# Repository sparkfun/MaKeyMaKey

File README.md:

**Note: Retired Product**
===========

This product has been retired from our catalog and is no longer for sale. This page is made available for those looking for datasheets and the simply curious. For the latest version of the board manufactured by JoyLabz, check out the [Makey Makey Classic by JoyLabz](https://www.sparkfun.com/products/14478).

---

MaKey MaKey
===========

[  
*MaKey MaKey - Standard Kit (WIG-11511)*](https://www.sparkfun.com/products/11511)

Using the MaKey MaKey you can *make* anything into a *key* (get it?) just by connecting a few alligator clips. The MaKey MaKey is an invention kit that tricks your computer into thinking that almost anything is a keyboard. This allows you to hook up all kinds of fun things as an input.

The MaKey MaKey uses high resistance switching to detect when you've made a connection even through materials that aren't very conductive (like leaves, pasta or people). This technique attracts noise on the input, so a moving window averager is used to lowpass the noise. The on-board ATMega32u4 communicates with your computer using the Human Interface Device (HID) protocol which means that it can act like a keyboard or mouse.

Repository Contents
-------------------
* **/Firmware** - Example firmware files
* **/Hardware** - All Eagle design files (.brd, .sch)
* **/Production** - Test bed files and production panel files

Documentation
--------------
* **[Makey Makey Quickstart Guide](https://learn.sparkfun.com/tutorials/makey-makey-quickstart-guide)** - Basic hookup guide for the Makey Makey.
* **[Makey Makey Advanced Guide](https://learn.sparkfun.com/tutorials/makey-makey-advanced-guide)** - Advanced hookup guide for the Makey Makey.

Product Versions
----------------

**[WIG-11511 (Retired)](https://www.sparkfun.com/products/11511) - Standard kit, OEM packaging**  
The standard kit includes the MaKey MaKey HID board, alligator clips, jumper wires, and a Mini-USB cable in OEM packaging.

**[WIG-11519 (Retired)](https://www.sparkfun.com/products/11519) - Deluxe kit, OEM packaging**  
The deluxe kit includes everything found in the standard kit along with an additional pack of alligator clips and a roll of copper wire (all in OEM packaging).

**[RTL-11437 (Retired)](https://www.sparkfun.com/products/11437) - Standard kit, retail packaging**  
This kit contains everything found in the standard kit and comes in retail-ready plastic packaging.

License Information
-------------------
The hardware is released under [Creative Commons ShareAlike 4.0 International](https://creativecommons.org/licenses/by-sa/4.0/).
The code is beerware; if you see me (or any other SparkFun employee) at the local, and you've found our code helpful, please buy us a round!

Distributed as-is; no warranty is given.

The MaKey MaKey is a collaboration with Jay Silver and Eric Rosenbaum. You can find more information about them [here](http://www.makeymakey.com/).

Makey Makey is a registered trademark of JoyLabz LLC.

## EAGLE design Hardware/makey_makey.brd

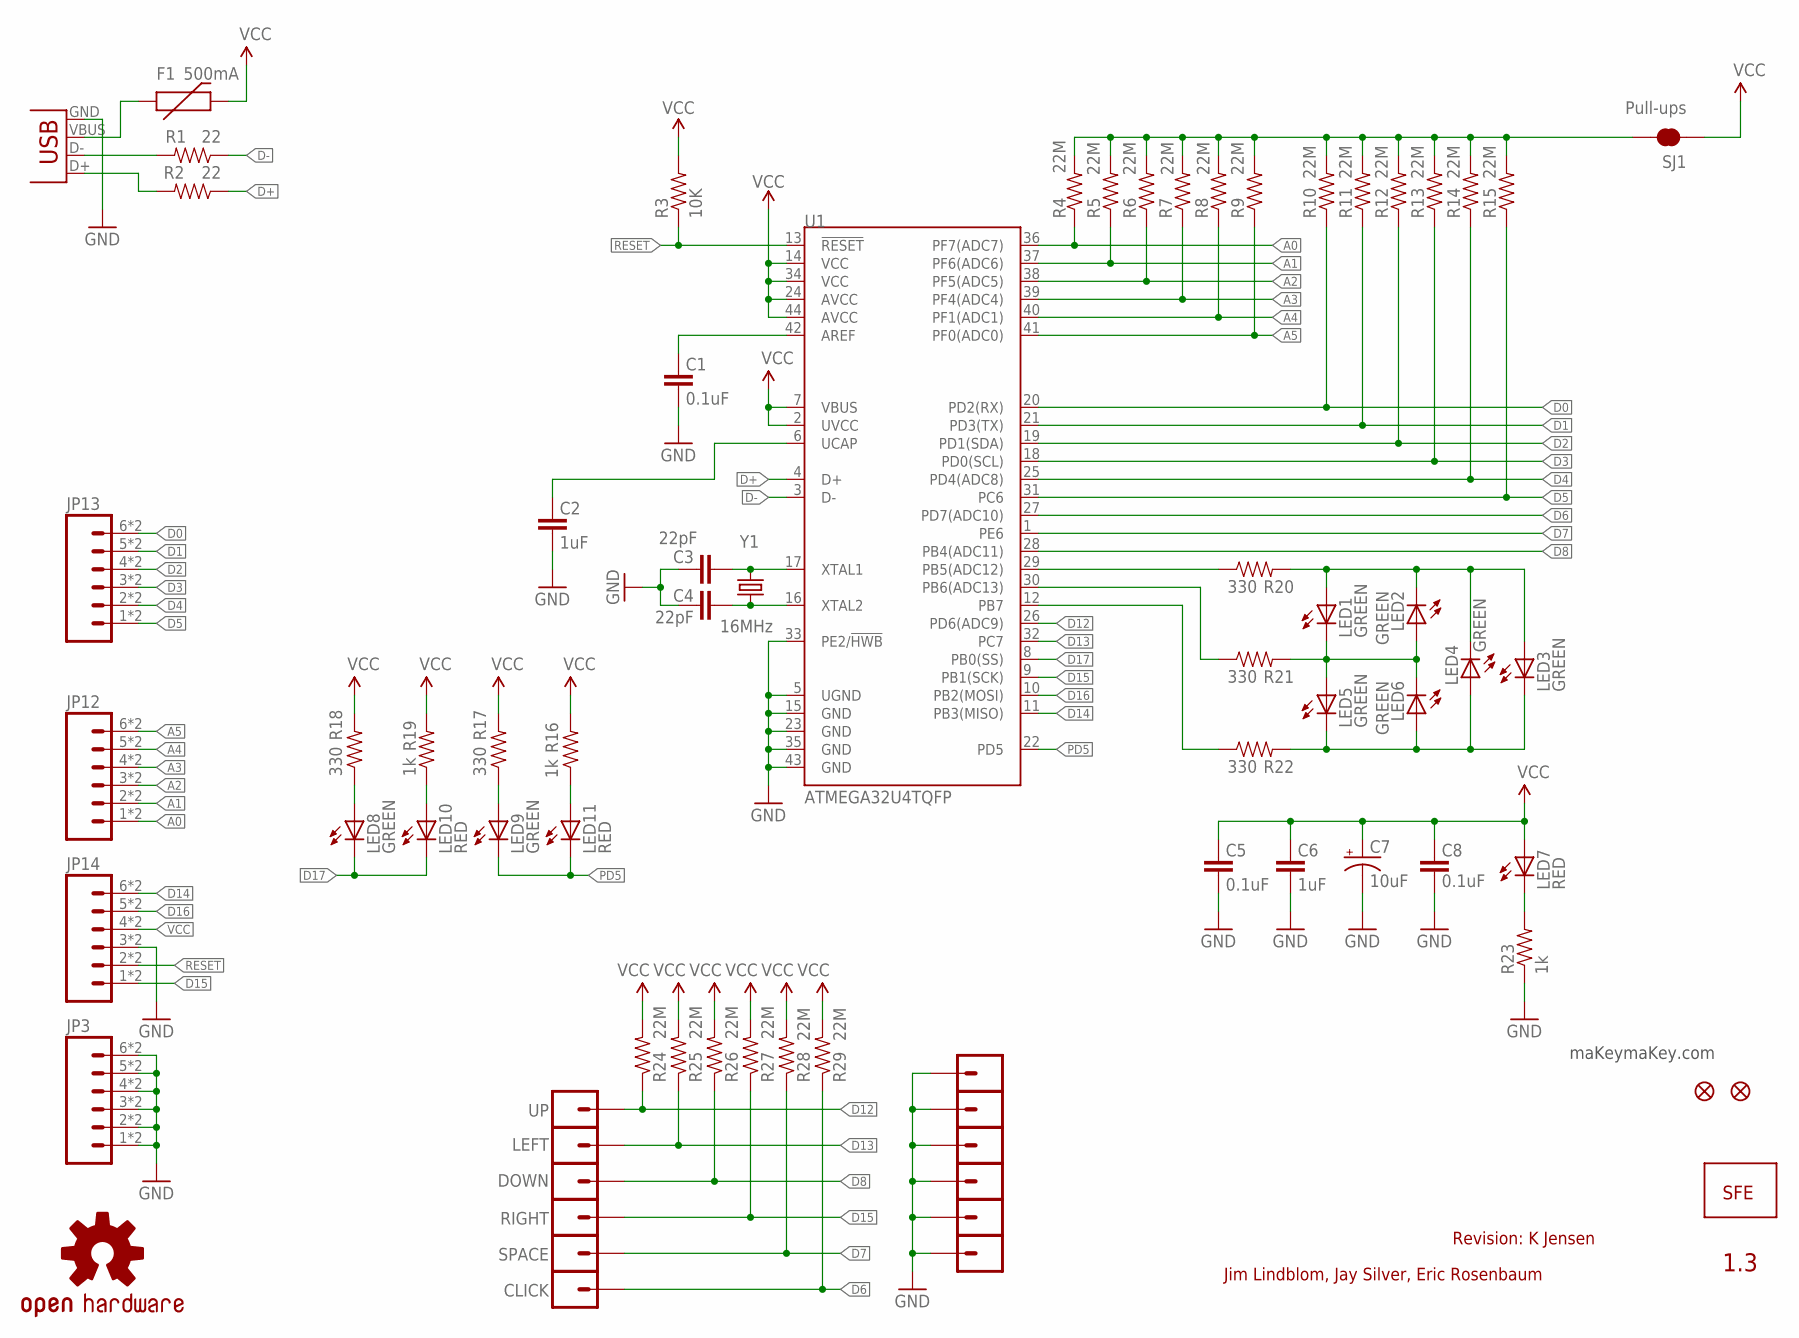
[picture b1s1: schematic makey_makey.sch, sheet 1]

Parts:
C1, C5, C8: 0.1uF; 0603-CAP
C2, C6: 1uF; 0603-CAP
C3, C4: 22pF; 0603-CAP
C7: 10uF; EIA3216
CLICK: M01ALLIGATOR-3MM; 1X01_ALLIGATOR_3MM
DOWN: M01ALLIGATOR-3MM; 1X01_ALLIGATOR_3MM
F1: 500mA; PTC-1206-WIDE
JP1, JP2: FIDUCIALUFIDUCIAL; MICRO-FIDUCIAL
JP3, JP12, JP13, JP14: M06SMD-STRAIGHT-COMBO; 1X06_SMD_STRAIGHT_COMBO
JP5, JP6, JP7, JP8, JP10, JP11: M01ALLIGATOR-3MM; 1X01_ALLIGATOR_3MM
JP9: LOGO-SFENEW; SFE-NEW-WEBLOGO
LED1, LED2, LED3, LED4, LED5, LED6: GREEN; LED-1206-BOTTOM
LED7, LED10, LED11: RED; LED-0603
LED8, LED9: GREEN; LED-0603
LEFT: M01ALLIGATOR-3MM; 1X01_ALLIGATOR_3MM
R1, R2: 22; 0603-RES
R3: 10K; 0603-RES
R4, R5, R6, R7, R8, R9, R10, R11, R12, R13, R14, R15, R24, R25, R26, R27, R28, R29: 22M; 0603-RES
R16, R19, R23: 1k; 0603-RES
R17, R18, R20, R21, R22: 330; 0603-RES
RIGHT: M01ALLIGATOR-3MM; 1X01_ALLIGATOR_3MM
SJ1: Pull-ups; SJ_2S-TRACE
SPACE: M01ALLIGATOR-3MM; 1X01_ALLIGATOR_3MM
U1: ATMEGA32U4TQFP; TQFP44
U$1: OSHW-LOGOM; OSHW-LOGO-M
UP: M01ALLIGATOR-3MM; 1X01_ALLIGATOR_3MM
X1: USBSMD; USB-MINIB
Y1: 16MHz; CRYSTAL-SMD-5X3

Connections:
A0: JP12.1, JP12.1-2 (1), R4.1, U1.36 (PF7(ADC7))
A1: JP12.2, JP12.2-2 (2), R5.1, U1.37 (PF6(ADC6))
A2: JP12.3, JP12.3-2 (3), R6.1, U1.38 (PF5(ADC5))
A3: JP12.4, JP12.4-2 (4), R7.1, U1.39 (PF4(ADC4))
A4: JP12.5, JP12.5-2 (5), R8.1, U1.40 (PF1(ADC1))
A5: JP12.6, JP12.6-2 (6), R9.1, U1.41 (PF0(ADC0))
AREF: C1.2, U1.42 (AREF)
D0: JP13.6, JP13.6-2 (6), R10.1, U1.20 (PD2(RX))
D1: JP13.5, JP13.5-2 (5), R11.1, U1.21 (PD3(TX))
D2: JP13.4, JP13.4-2 (4), R12.1, U1.19 (PD1(SDA))
D3: JP13.3, JP13.3-2 (3), R13.1, U1.18 (PD0(SCL))
D4: JP13.2, JP13.2-2 (2), R14.1, U1.25 (PD4(ADC8))
D5: JP13.1, JP13.1-2 (1), R15.1, U1.31 (PC6)
D6: CLICK.1@0, CLICK.1@2, R29.1, U1.27 (PD7(ADC10))
D7: R28.1, SPACE.1@0, SPACE.1@2, U1.1 (PE6)
D8: DOWN.1@0, DOWN.1@2, R26.1, U1.28 (PB4(ADC11))
D9: R20.1, U1.29 (PB5(ADC12))
D10: R21.1, U1.30 (PB6(ADC13))
D11: R22.1, U1.12 (PB7)
D12: R24.1, U1.26 (PD6(ADC9)), UP.1@0, UP.1@2
D13: LEFT.1@0, LEFT.1@2, R25.1, U1.32 (PC7)
D14: JP14.6, JP14.6-2 (6), U1.11 (PB3(MISO))
D15: JP14.1, JP14.1-2 (1), R27.1, RIGHT.1@0, RIGHT.1@2, U1.9 (PB1(SCK))
D16: JP14.5, JP14.5-2 (5), U1.10 (PB2(MOSI))
D17: LED8.C, LED10.C, U1.8 (PB0(SS))
D+: R2.1, U1.4 (D+)
D-: R1.1, U1.3 (D-)
GND: C1.1, C2.1, C3.2, C4.2, C5.1, C6.1, C7.C (-), C8.1, JP3.1, JP3.1-2 (1), JP3.2, JP3.2-2 (2), JP3.3, JP3.3-2 (3), JP3.4, JP3.4-2 (4), JP3.5, JP3.5-2 (5), JP3.6, JP3.6-2 (6), JP5.1@0, JP5.1@2, JP6.1@0, JP6.1@2, JP7.1@0, JP7.1@2, JP8.1@0, JP8.1@2, JP10.1@0, JP10.1@2, JP11.1@0, JP11.1@2, JP14.3, JP14.3-2 (3), R23.1, U1.5 (UGND), U1.15 (GND), U1.23 (GND), U1.33 (PE2/!HWB), U1.35 (GND), U1.43 (GND), X1.GND
unnamed: C4.1, U1.16 (XTAL2), Y1.1
unnamed: C3.1, U1.17 (XTAL1), Y1.3 (2)
unnamed: LED8.A, R18.1
unnamed: C2.2, U1.6 (UCAP)
unnamed: F1.1, X1.VBUS
unnamed: R1.2, X1.D-
unnamed: LED7.C, R23.2
unnamed: R2.2, X1.D+
unnamed: LED11.A, R16.1
unnamed: LED10.A, R19.1
unnamed: LED9.A, R17.1
unnamed: LED1.C, LED2.A, LED5.A, LED6.C, R21.2
unnamed: LED1.A, LED2.C, LED3.A, LED4.C, R20.2
unnamed: LED3.C, LED4.A, LED5.C, LED6.A, R22.2
PD5: LED9.C, LED11.C, U1.22 (PD5)
PULL-UP: R4.2, R5.2, R6.2, R7.2, R8.2, R9.2, R10.2, R11.2, R12.2, R13.2, R14.2, R15.2, SJ1.2
RESET: JP14.2, JP14.2-2 (2), R3.1, U1.13 (!RESET)
VCC: C5.2, C6.2, C7.A (+), C8.2, F1.2, JP14.4, JP14.4-2 (4), LED7.A, R3.2, R16.2, R17.2, R18.2, R19.2, R24.2, R25.2, R26.2, R27.2, R28.2, R29.2, SJ1.1, U1.2 (UVCC), U1.7 (VBUS), U1.14 (VCC), U1.24 (AVCC), U1.34 (VCC), U1.44 (AVCC)

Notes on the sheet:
1.3
Jim Lindblom, Jay Silver, Eric Rosenbaum
maKeymaKey.com
Revision: K Jensen

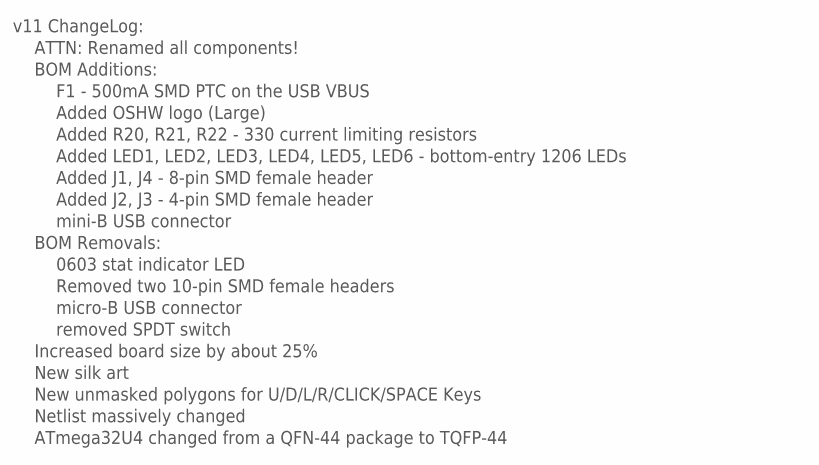
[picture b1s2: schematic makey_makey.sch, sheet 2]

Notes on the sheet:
v11 ChangeLog:
BOM Additions:
F1 - 500mA SMD PTC on the USB VBUS
Added OSHW logo (Large)
ATTN: Renamed all components!
Added R20, R21, R22 - 330 current limiting resistors
Added LED1, LED2, LED3, LED4, LED5, LED6 - bottom-entry 1206 LEDs
BOM Removals:
0603 stat indicator LED
Increased board size by about 25%
New silk art
Netlist massively changed
Removed two 10-pin SMD female headers
Added J1, J4 - 8-pin SMD female header
Added J2, J3 - 4-pin SMD female header
ATmega32U4 changed from a QFN-44 package to TQFP-44
New unmasked polygons for U/D/L/R/CLICK/SPACE Keys
mini-B USB connector
micro-B USB connector
removed SPDT switch

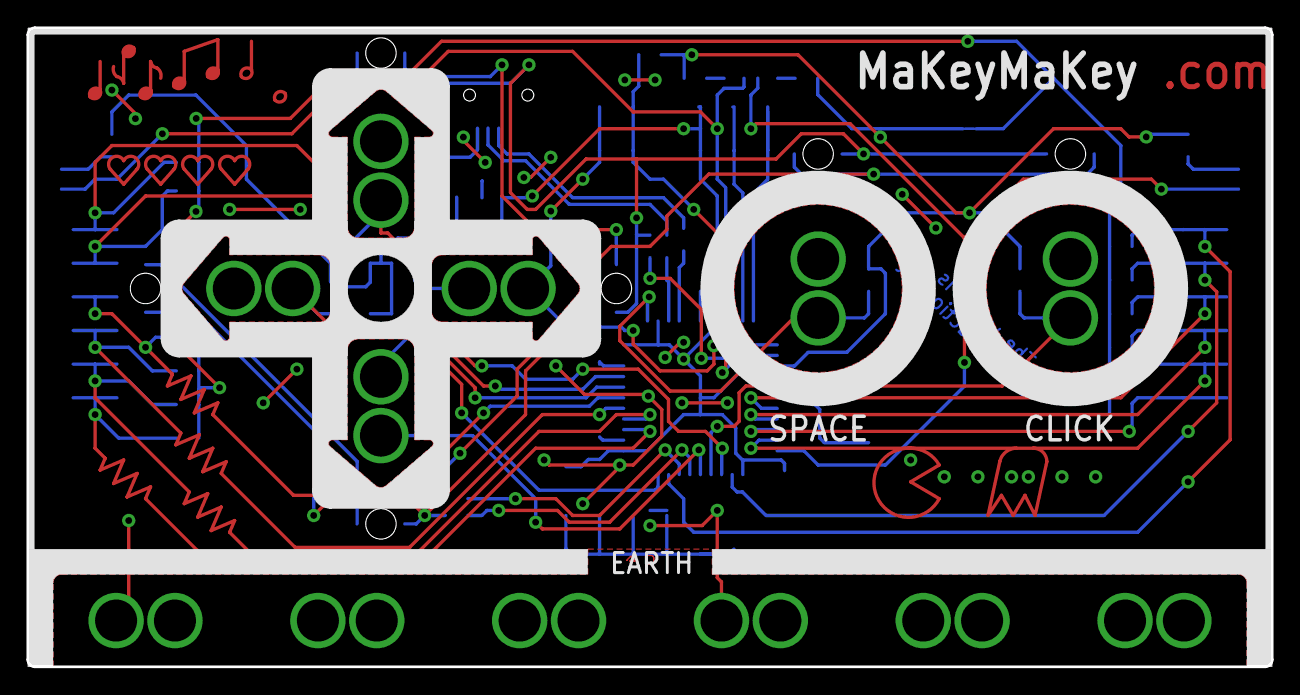
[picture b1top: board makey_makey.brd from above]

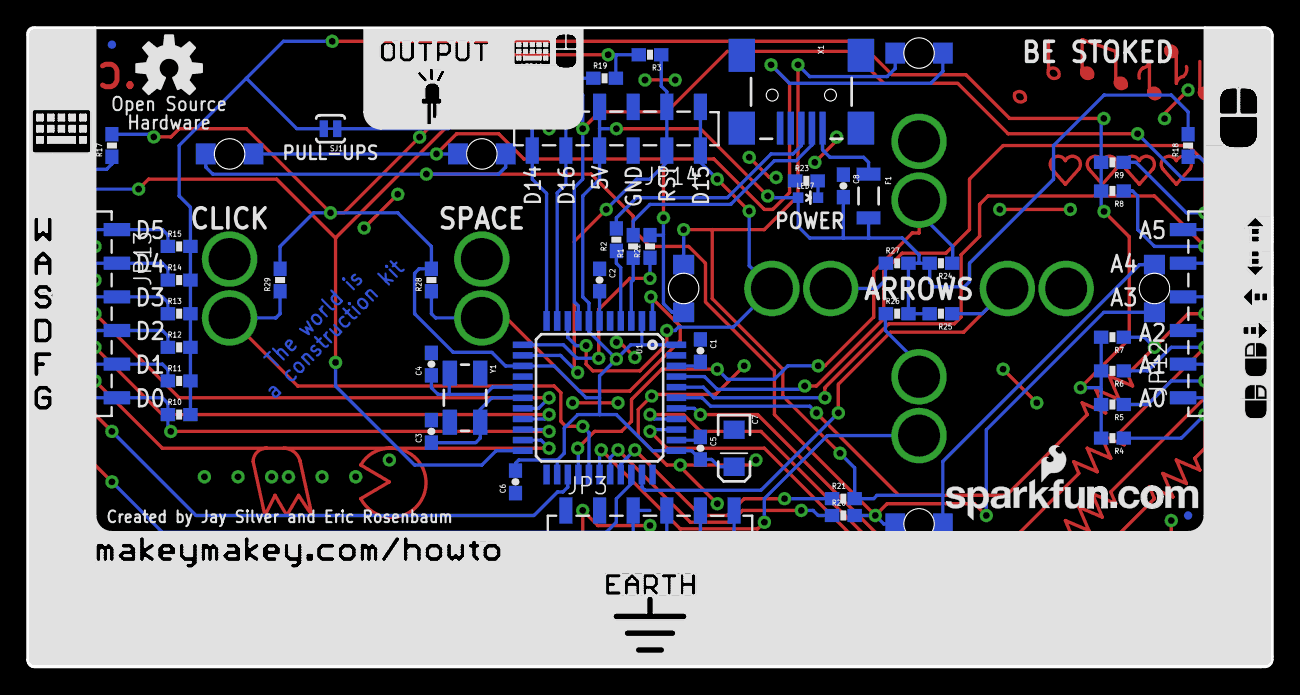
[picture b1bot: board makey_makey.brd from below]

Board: 2 copper layers, 94.0 x 48.3 mm, 73 parts (63 on the bottom side), 46 nets.

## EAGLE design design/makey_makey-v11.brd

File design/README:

Eagle design files for the MaKey MaKey PCB.

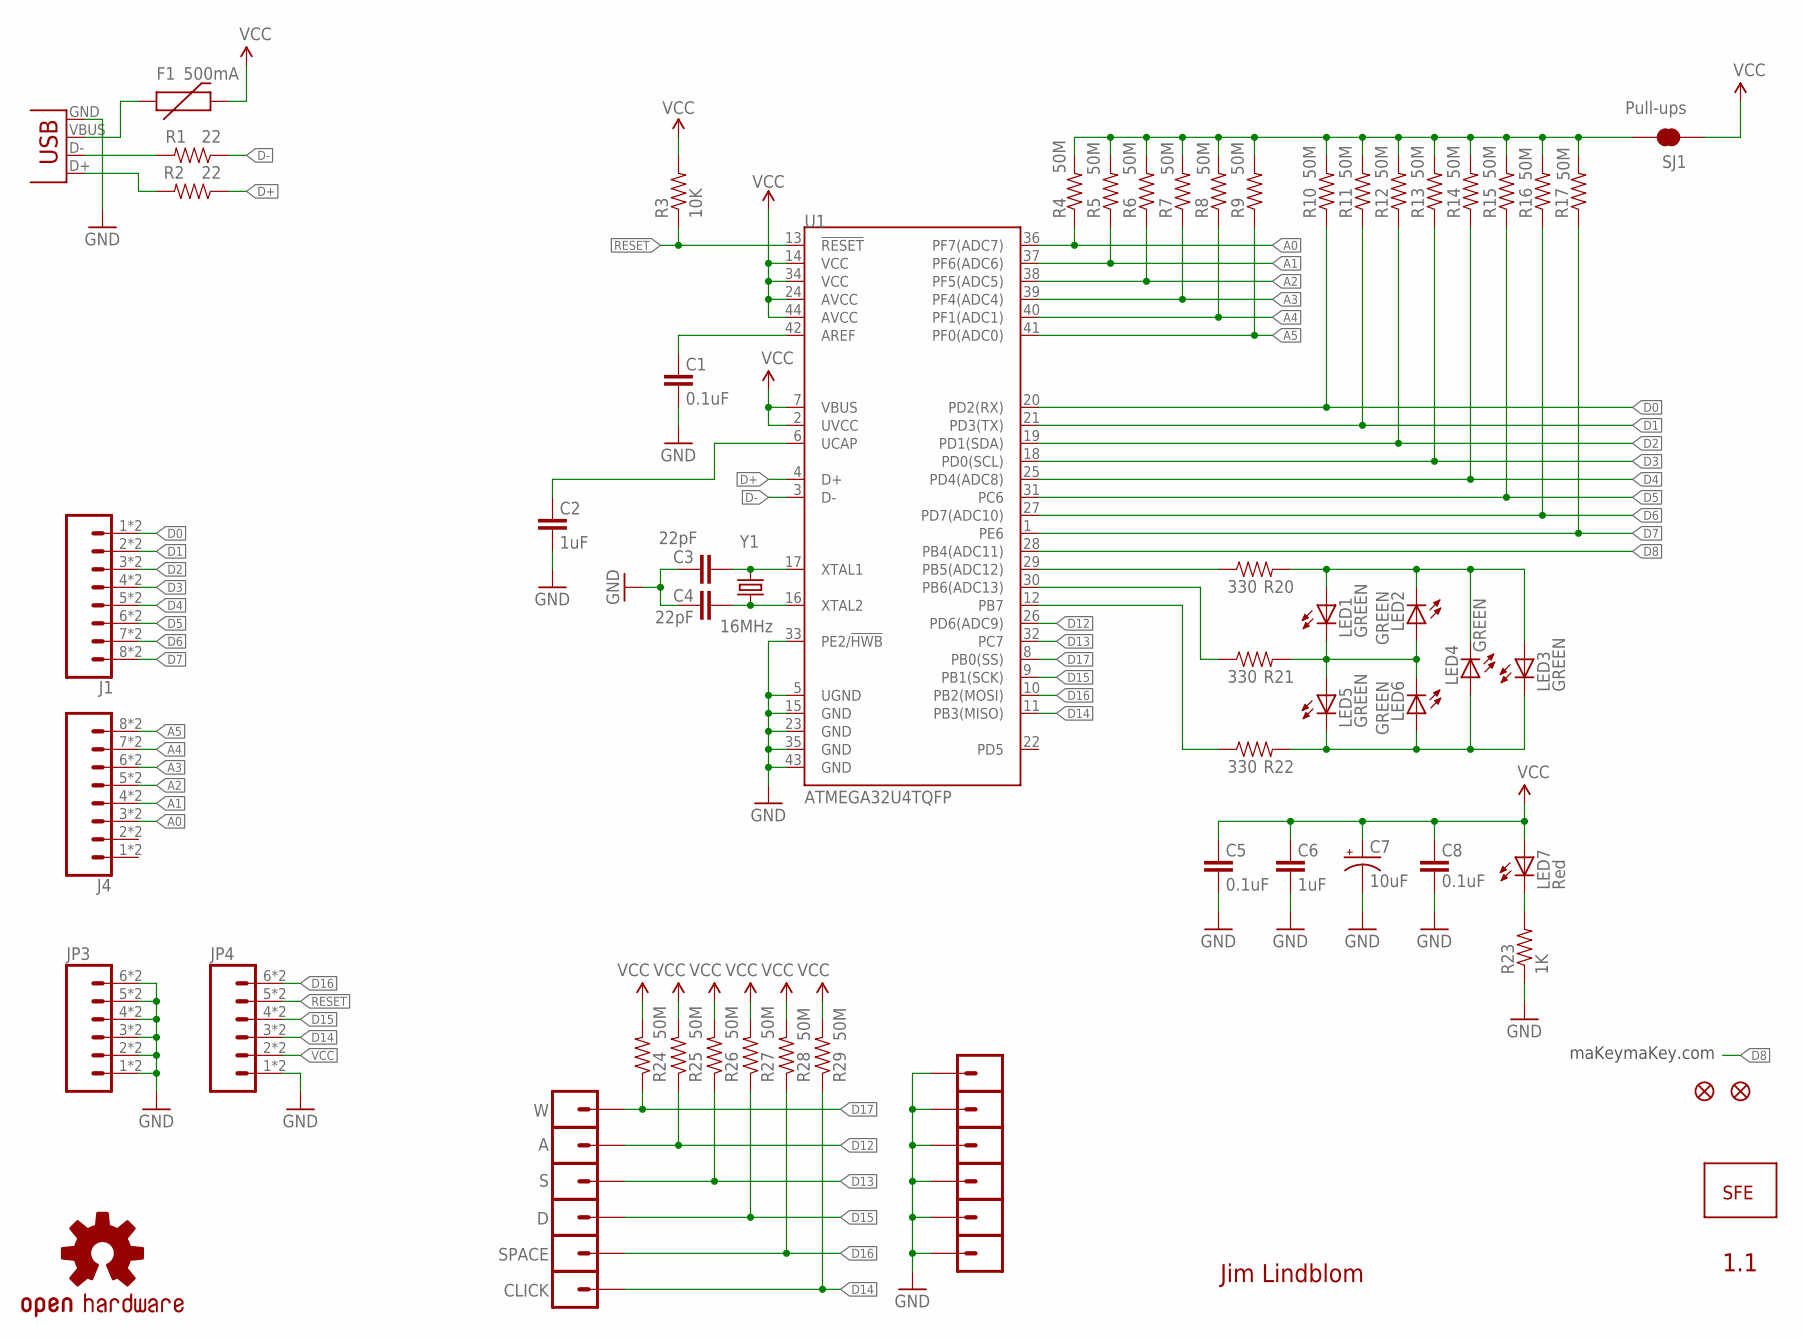
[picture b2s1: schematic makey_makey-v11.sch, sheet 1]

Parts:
A: M01ALLIGATOR-3MM; 1X01_ALLIGATOR_3MM
C1, C5, C8: 0.1uF; 0402-CAP
C2, C6: 1uF; 0402-CAP
C3, C4: 22pF; 0402-CAP
C7: 10uF; EIA3216
CLICK: M01ALLIGATOR-3MM; 1X01_ALLIGATOR_3MM
D: M01ALLIGATOR-3MM; 1X01_ALLIGATOR_3MM
F1: 500mA; PTC-1206
J1, J4: M08SMD-COMBO; 1X08_SMD_COMBINED
JP1, JP2: FIDUCIALUFIDUCIAL; MICRO-FIDUCIAL
JP3, JP4: M06SMD-STRAIGHT-COMBO; 1X06_SMD_STRAIGHT_COMBO
JP5, JP6, JP7, JP8, JP10, JP11: M01ALLIGATOR-3MM; 1X01_ALLIGATOR_3MM
JP9: LOGO-SFENEW; SFE-NEW-WEBLOGO
LED1, LED2, LED3, LED4, LED5, LED6: GREEN; LED-1206-BOTTOM
LED7: Red; LED-0603
R1, R2: 22; 0402-RES
R3: 10K; 0402-RES
R4, R5, R6, R7, R8, R9, R10, R11, R12, R13, R14, R15, R16, R17, R24, R25, R26, R27, R28, R29: 50M; 0402-RES
R20, R21, R22: 330; 0402-RES
R23: 1K; 0402-RES
S: M01ALLIGATOR-3MM; 1X01_ALLIGATOR_3MM
SJ1: Pull-ups; SJ_2S-TRACE
SPACE: M01ALLIGATOR-3MM; 1X01_ALLIGATOR_3MM
U1: ATMEGA32U4TQFP; TQFP44
U$1: OSHW-LOGOL; OSHW-LOGO-L
W: M01ALLIGATOR-3MM; 1X01_ALLIGATOR_3MM
X1: USBSMD; USB-MINIB
Y1: 16MHz; CRYSTAL-SMD-5X3

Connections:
A0: J4.3, J4.3@2 (3), R4.1, U1.36 (PF7(ADC7))
A1: J4.4, J4.4@2 (4), R5.1, U1.37 (PF6(ADC6))
A2: J4.5, J4.5@2 (5), R6.1, U1.38 (PF5(ADC5))
A3: J4.6, J4.6@2 (6), R7.1, U1.39 (PF4(ADC4))
A4: J4.7, J4.7@2 (7), R8.1, U1.40 (PF1(ADC1))
A5: J4.8, J4.8@2 (8), R9.1, U1.41 (PF0(ADC0))
AREF: C1.2, U1.42 (AREF)
D0: J1.1, J1.1@2 (1), R10.1, U1.20 (PD2(RX))
D1: J1.2, J1.2@2 (2), R11.1, U1.21 (PD3(TX))
D2: J1.3, J1.3@2 (3), R12.1, U1.19 (PD1(SDA))
D3: J1.4, J1.4@2 (4), R13.1, U1.18 (PD0(SCL))
D4: J1.5, J1.5@2 (5), R14.1, U1.25 (PD4(ADC8))
D5: J1.6, J1.6@2 (6), R15.1, U1.31 (PC6)
D6: J1.7, J1.7@2 (7), R16.1, U1.27 (PD7(ADC10))
D7: J1.8, J1.8@2 (8), R17.1, U1.1 (PE6)
D8: U1.28 (PB4(ADC11))
D9: R20.1, U1.29 (PB5(ADC12))
D10: R21.1, U1.30 (PB6(ADC13))
D11: R22.1, U1.12 (PB7)
D12: A.1@0, A.1@2, R25.1, U1.26 (PD6(ADC9))
D13: R26.1, S.1@0, S.1@2, U1.32 (PC7)
D14: CLICK.1@0, CLICK.1@2, JP4.3, JP4.3-2 (3), R29.1, U1.11 (PB3(MISO))
D15: D.1@0, D.1@2, JP4.4, JP4.4-2 (4), R27.1, U1.9 (PB1(SCK))
D16: JP4.6, JP4.6-2 (6), R28.1, SPACE.1@0, SPACE.1@2, U1.10 (PB2(MOSI))
D17: R24.1, U1.8 (PB0(SS)), W.1@0, W.1@2
D+: R2.1, U1.4 (D+)
D-: R1.1, U1.3 (D-)
GND: C1.1, C2.1, C3.2, C4.2, C5.1, C6.1, C7.C (-), C8.1, JP3.1, JP3.1-2 (1), JP3.2, JP3.2-2 (2), JP3.3, JP3.3-2 (3), JP3.4, JP3.4-2 (4), JP3.5, JP3.5-2 (5), JP3.6, JP3.6-2 (6), JP4.1, JP4.1-2 (1), JP5.1@0, JP5.1@2, JP6.1@0, JP6.1@2, JP7.1@0, JP7.1@2, JP8.1@0, JP8.1@2, JP10.1@0, JP10.1@2, JP11.1@0, JP11.1@2, R23.1, U1.5 (UGND), U1.15 (GND), U1.23 (GND), U1.33 (PE2/!HWB), U1.35 (GND), U1.43 (GND), X1.GND
unnamed: C4.1, U1.16 (XTAL2), Y1.1
unnamed: C3.1, U1.17 (XTAL1), Y1.3 (2)
unnamed: R4.2, R5.2, R6.2, R7.2, R8.2, R9.2, R10.2, R11.2, R12.2, R13.2, R14.2, R15.2, R16.2, R17.2, SJ1.2
unnamed: C2.2, U1.6 (UCAP)
unnamed: F1.1, X1.VBUS
unnamed: R1.2, X1.D-
unnamed: LED7.C, R23.2
unnamed: R2.2, X1.D+
unnamed: LED1.C, LED2.A, LED5.A, LED6.C, R21.2
unnamed: LED1.A, LED2.C, LED3.A, LED4.C, R20.2
unnamed: LED3.C, LED4.A, LED5.C, LED6.A, R22.2
RESET: JP4.5, JP4.5-2 (5), R3.1, U1.13 (!RESET)
VCC: C5.2, C6.2, C7.A (+), C8.2, F1.2, JP4.2, JP4.2-2 (2), LED7.A, R3.2, R24.2, R25.2, R26.2, R27.2, R28.2, R29.2, SJ1.1, U1.2 (UVCC), U1.7 (VBUS), U1.14 (VCC), U1.24 (AVCC), U1.34 (VCC), U1.44 (AVCC)

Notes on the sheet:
1.1
Jim Lindblom
maKeymaKey.com

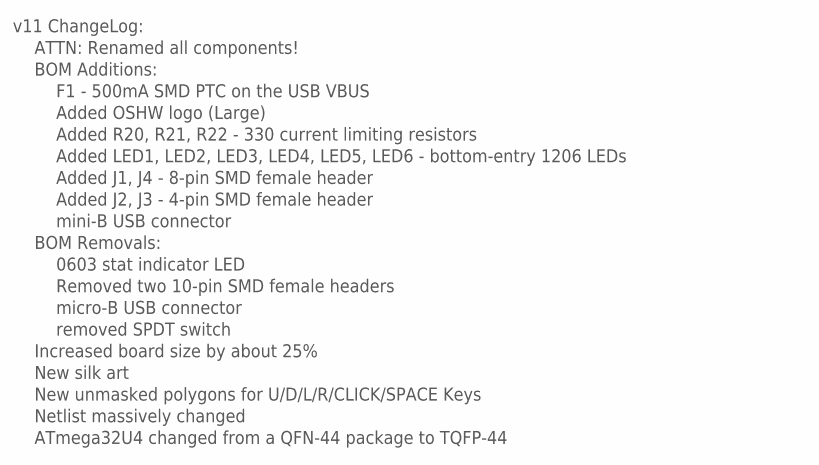
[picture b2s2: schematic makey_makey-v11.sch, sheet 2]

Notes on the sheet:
v11 ChangeLog:
BOM Additions:
F1 - 500mA SMD PTC on the USB VBUS
Added OSHW logo (Large)
ATTN: Renamed all components!
Added R20, R21, R22 - 330 current limiting resistors
Added LED1, LED2, LED3, LED4, LED5, LED6 - bottom-entry 1206 LEDs
BOM Removals:
0603 stat indicator LED
Increased board size by about 25%
New silk art
Netlist massively changed
Removed two 10-pin SMD female headers
Added J1, J4 - 8-pin SMD female header
Added J2, J3 - 4-pin SMD female header
ATmega32U4 changed from a QFN-44 package to TQFP-44
New unmasked polygons for U/D/L/R/CLICK/SPACE Keys
mini-B USB connector
micro-B USB connector
removed SPDT switch

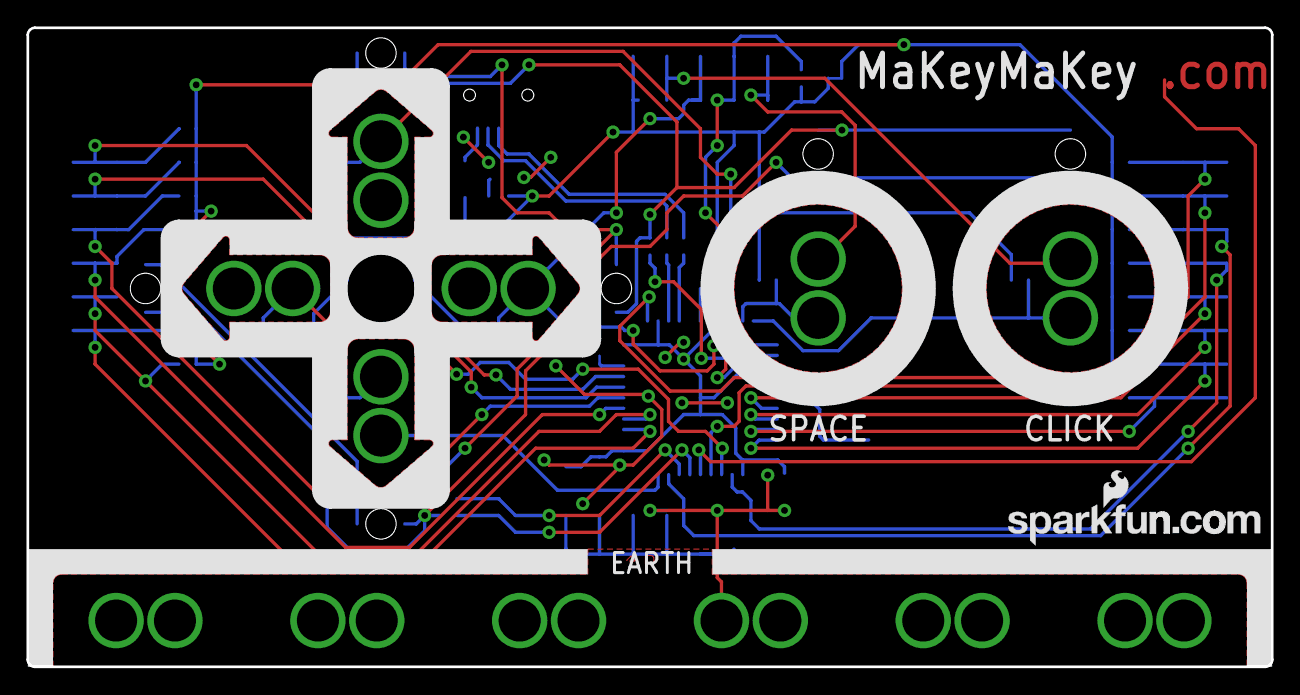
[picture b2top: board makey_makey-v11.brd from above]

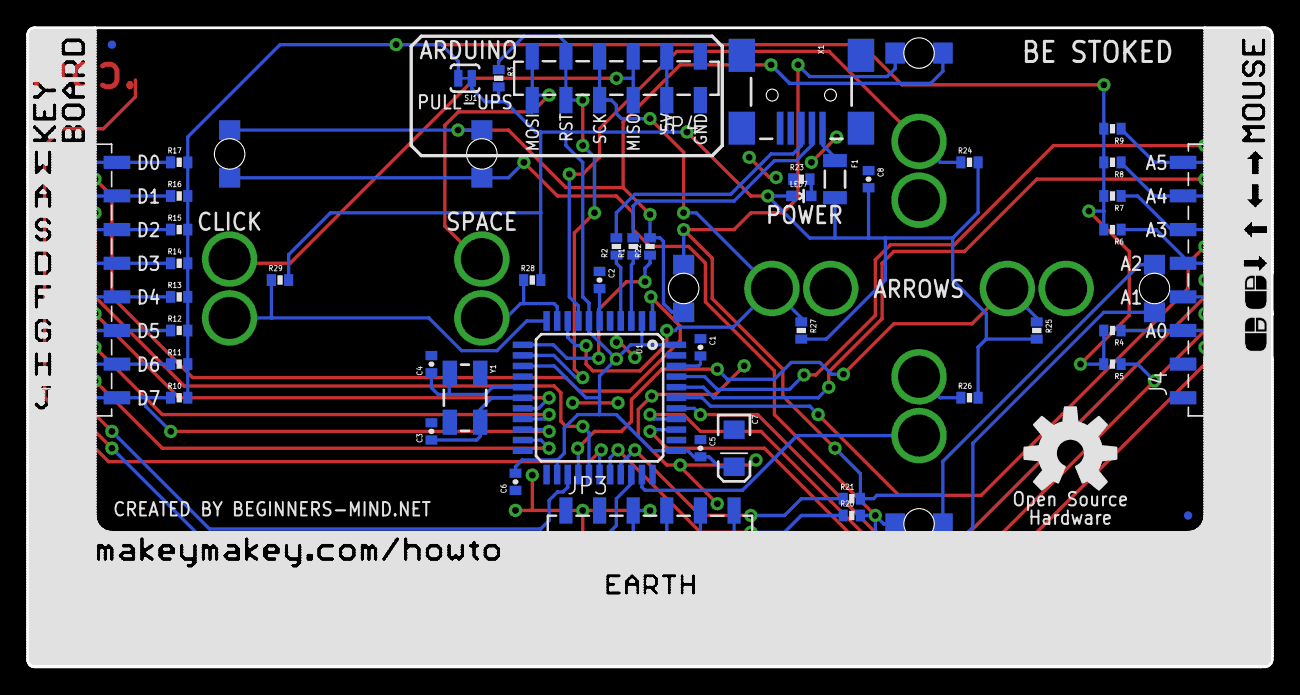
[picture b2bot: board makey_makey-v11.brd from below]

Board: 2 copper layers, 94.0 x 48.3 mm, 67 parts (56 on the bottom side), 40 nets.

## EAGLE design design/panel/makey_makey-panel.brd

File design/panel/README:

Panelized design files for MaKey MaKey PCB. Two PCB's per panel.

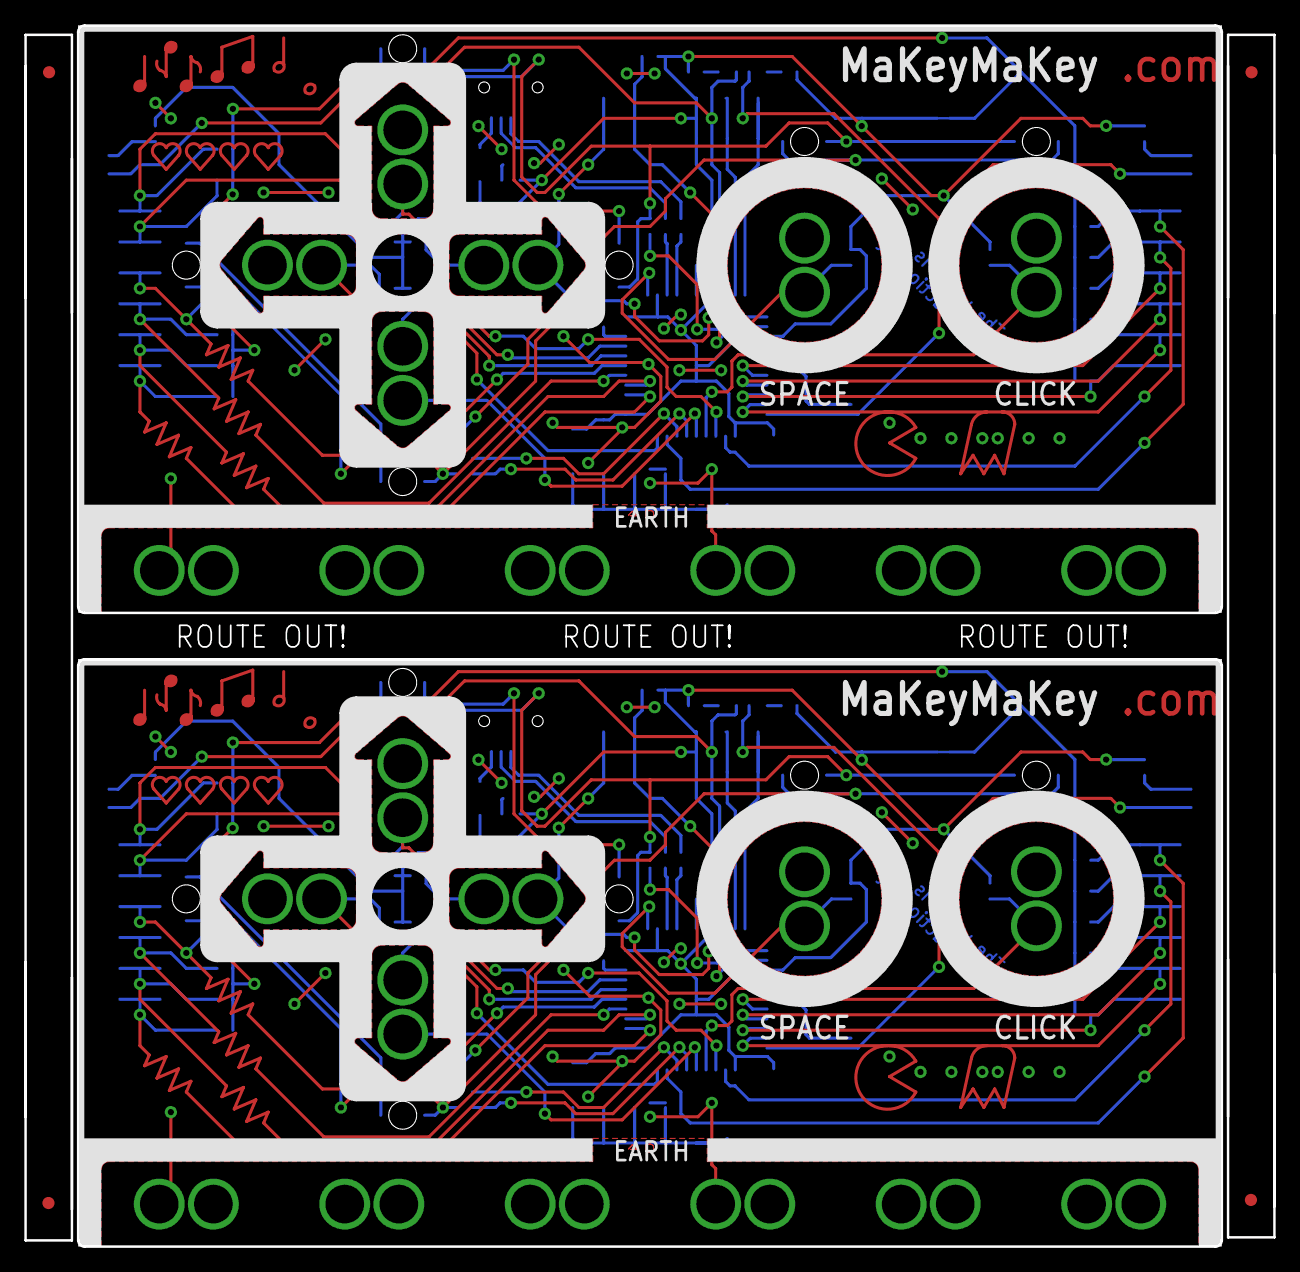
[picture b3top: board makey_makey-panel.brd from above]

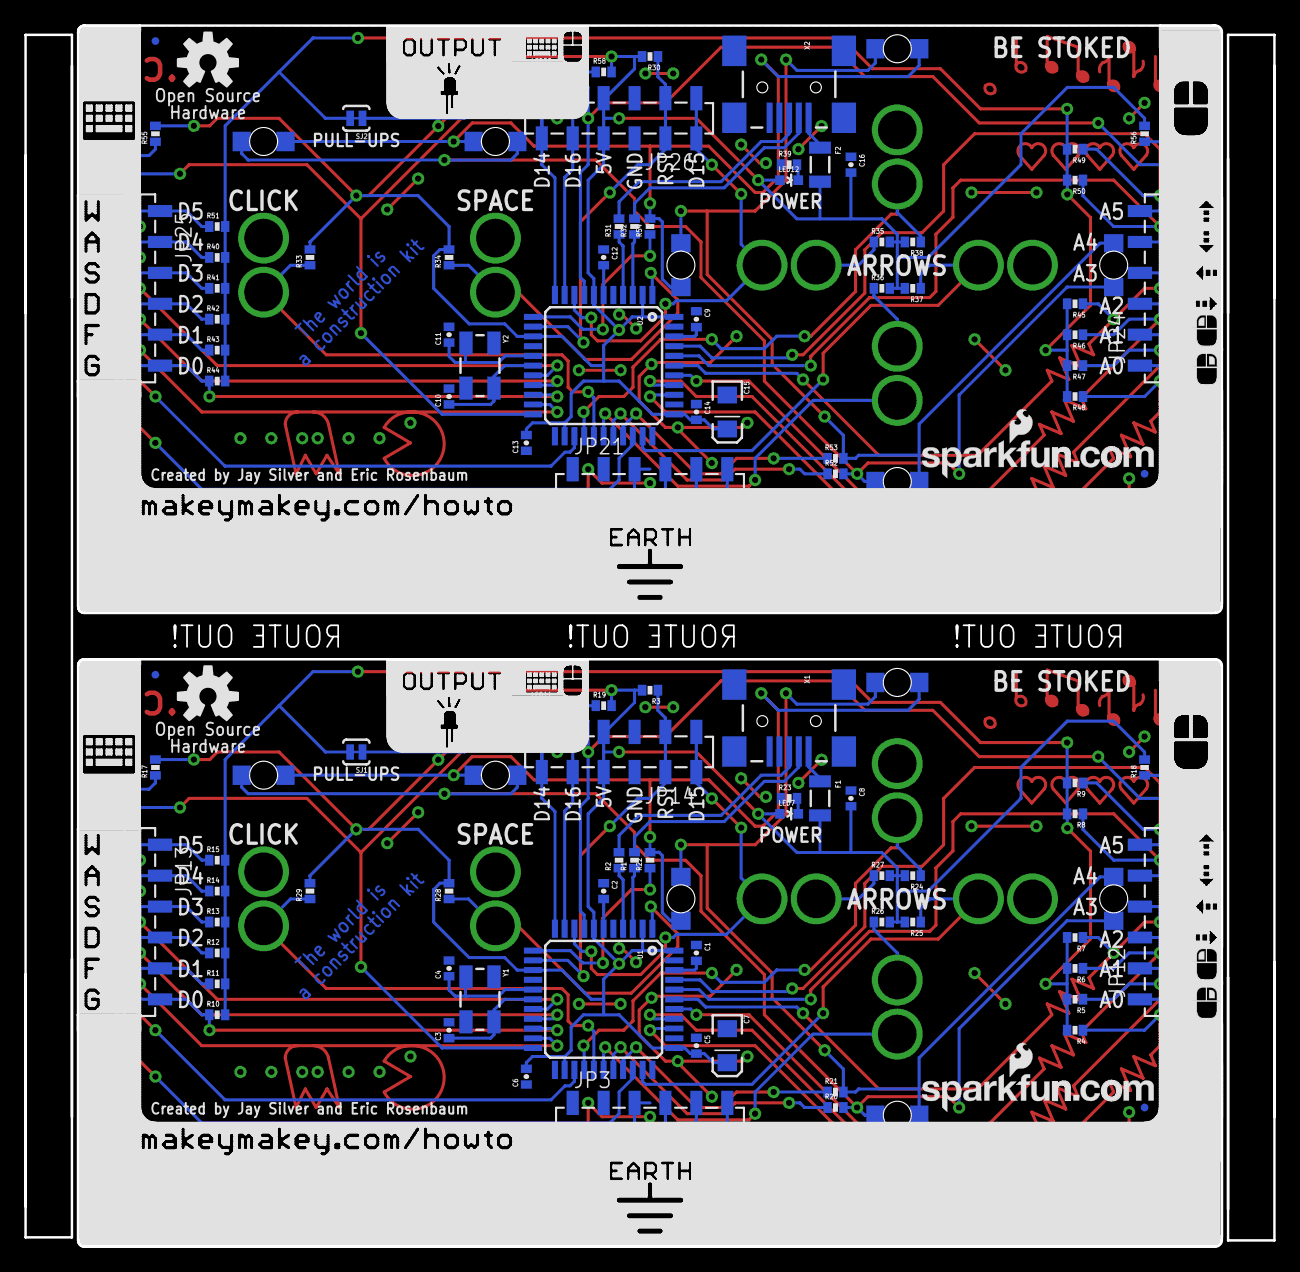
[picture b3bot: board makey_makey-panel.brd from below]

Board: 2 copper layers, 102.6 x 100.3 mm, 150 parts (126 on the bottom side), 92 nets.

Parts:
C1, C5, C8, C9, C14, C16: 0.1uF; 0402-CAP
C2, C6, C12, C13: 1uF; 0402-CAP
C3, C4, C10, C11: 22pF; 0402-CAP
C7, C15: 10uF; EIA3216
CLICK, CLICK1: 1X01_ALLIGATOR_3MM
DOWN, DOWN1: 1X01_ALLIGATOR_3MM
E$1, E$2, E$3, E$4: FIDUCIAL-1X2
F1, F2: 500mA; PTC-1206
JP1, JP2, JP22, JP23: FIDUCIALUFIDUCIAL; MICRO-FIDUCIAL
JP3, JP12, JP13, JP14, JP21, JP24, JP25, JP26: 1X06_SMD_STRAIGHT_COMBO
JP4, JP9: LOGO-SFENEW; SFE-NEW-WEBLOGO
JP5, JP6, JP7, JP8, JP10, JP11, JP15, JP16, JP17, JP18, JP19, JP20: 1X01_ALLIGATOR_3MM
LED1, LED2, LED3, LED4, LED5, LED6, LED13, LED14, LED15, LED16, LED17, LED18: GREEN; LED-1206-BOTTOM
LED7, LED10, LED11, LED12, LED21, LED22: RED; LED-0603
LED8, LED9, LED19, LED20: GREEN; LED-0603
LEFT, LEFT1: 1X01_ALLIGATOR_3MM
R1, R2, R31, R32: 22; 0402-RES
R3, R30: 10K; 0402-RES
R4, R5, R6, R7, R8, R9, R10, R11, R12, R13, R14, R15, R24, R25, R26, R27, R28, R29, R33, R34, R35, R36, R37, R38, R40, R41, R42, R43, R44, R45, R46, R47, R48, R49, R50, R51: 22M; 0402-RES
R16, R19, R23, R39, R57, R58: 1k; 0402-RES
R17, R18, R20, R21, R22, R52, R53, R54, R55, R56: 330; 0402-RES
RIGHT, RIGHT1: 1X01_ALLIGATOR_3MM
SJ1, SJ2: Pull-ups; SJ_2S-TRACE
SPACE, SPACE1: 1X01_ALLIGATOR_3MM
U1, U2: ATMEGA32U4TQFP; TQFP44
U$1, U$2: OSHW-LOGOM; OSHW-LOGO-M
UP, UP1: 1X01_ALLIGATOR_3MM
X1, X2: USBSMD; USB-MINIB
Y1, Y2: 16MHz; CRYSTAL-SMD-5X3

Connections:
A0: JP12.1, JP12.1-2, R4.1, U1.36
A1: JP12.2, JP12.2-2, R5.1, U1.37
A2: JP12.3, JP12.3-2, R6.1, U1.38
A3: JP12.4, JP12.4-2, R7.1, U1.39
A4: JP12.5, JP12.5-2, R8.1, U1.40
A5: JP12.6, JP12.6-2, R9.1, U1.41
A6: JP24.1, JP24.1-2, R48.1, U2.36
A7: JP24.2, JP24.2-2, R47.1, U2.37
A8: JP24.3, JP24.3-2, R46.1, U2.38
A9: JP24.4, JP24.4-2, R45.1, U2.39
A10: JP24.5, JP24.5-2, R50.1, U2.40
A11: JP24.6, JP24.6-2, R49.1, U2.41
AREF: C1.2, U1.42
AREF1: C9.2, U2.42
D0: JP13.6, JP13.6-2, R10.1, U1.20
D1: JP13.5, JP13.5-2, R11.1, U1.21
D2: JP13.4, JP13.4-2, R12.1, U1.19
D3: JP13.3, JP13.3-2, R13.1, U1.18
D4: JP13.2, JP13.2-2, R14.1, U1.25
D5: JP13.1, JP13.1-2, R15.1, U1.31
D6: CLICK.1@0, CLICK.1@2, R29.1, U1.27
D7: R28.1, SPACE.1@0, SPACE.1@2, U1.1
D8: DOWN.1@0, DOWN.1@2, R26.1, U1.28
D9: R20.1, U1.29
D10: R21.1, U1.30
D11: R22.1, U1.12
D12: R24.1, U1.26, UP.1@0, UP.1@2
D13: LEFT.1@0, LEFT.1@2, R25.1, U1.32
D14: JP14.6, JP14.6-2, U1.11
D15: JP14.1, JP14.1-2, R27.1, RIGHT.1@0, RIGHT.1@2, U1.9
D16: JP14.5, JP14.5-2, U1.10
D17: LED8.C, LED10.C, U1.8
D18: JP26.5, JP26.5-2, U2.10
D19: JP26.6, JP26.6-2, U2.11
D20: JP26.1, JP26.1-2, R35.1, RIGHT1.1@0, RIGHT1.1@2, U2.9
D21: JP25.6, JP25.6-2, R44.1, U2.20
D22: JP25.5, JP25.5-2, R43.1, U2.21
D23: JP25.4, JP25.4-2, R42.1, U2.19
D24: JP25.3, JP25.3-2, R41.1, U2.18
D25: JP25.2, JP25.2-2, R40.1, U2.25
D26: R34.1, SPACE1.1@0, SPACE1.1@2, U2.1
D27: R54.1, U2.12
D28: R38.1, U2.26, UP1.1@0, UP1.1@2
D29: LED19.C, LED21.C, U2.8
D30: LEFT1.1@0, LEFT1.1@2, R37.1, U2.32
D31: R53.1, U2.30
D32: R52.1, U2.29
D33: DOWN1.1@0, DOWN1.1@2, R36.1, U2.28
D34: CLICK1.1@0, CLICK1.1@2, R33.1, U2.27
D35: JP25.1, JP25.1-2, R51.1, U2.31
D+: R2.1, U1.4
D+1: R31.1, U2.4
D-: R1.1, U1.3
D-1: R32.1, U2.3
GND: C1.1, C2.1, C3.2, C4.2, C5.1, C6.1, C7.C, C8.1, JP3.1, JP3.1-2, JP3.2, JP3.2-2, JP3.3, JP3.3-2, JP3.4, JP3.4-2, JP3.5, JP3.5-2, JP3.6, JP3.6-2, JP5.1@0, JP5.1@2, JP6.1@0, JP6.1@2, JP7.1@0, JP7.1@2, JP8.1@0, JP8.1@2, JP10.1@0, JP10.1@2, JP11.1@0, JP11.1@2, JP14.3, JP14.3-2, R23.1, U1.5, U1.15, U1.23, U1.33, U1.35, U1.43, X1.GND
GND1: C9.1, C10.2, C11.2, C12.1, C13.1, C14.1, C15.C, C16.1, JP15.1@0, JP15.1@2, JP16.1@0, JP16.1@2, JP17.1@0, JP17.1@2, JP18.1@0, JP18.1@2, JP19.1@0, JP19.1@2, JP20.1@0, JP20.1@2, JP21.1, JP21.1-2, JP21.2, JP21.2-2, JP21.3, JP21.3-2, JP21.4, JP21.4-2, JP21.5, JP21.5-2, JP21.6, JP21.6-2, JP26.3, JP26.3-2, R39.1, U2.5, U2.15, U2.23, U2.33, U2.35, U2.43, X2.GND
unnamed: C4.1, U1.16, Y1.1
unnamed: C3.1, U1.17, Y1.3
unnamed: LED8.A, R18.1
unnamed: C2.2, U1.6
unnamed: F1.1, X1.VBUS
unnamed: R1.2, X1.D-
unnamed: LED7.C, R23.2
unnamed: R2.2, X1.D+
unnamed: LED11.A, R16.1
unnamed: LED10.A, R19.1
unnamed: LED9.A, R17.1
unnamed: C11.1, U2.16, Y2.1
unnamed: C10.1, U2.17, Y2.3
unnamed: C12.2, U2.6
unnamed: LED1.C, LED2.A, LED5.A, LED6.C, R21.2
unnamed: LED1.A, LED2.C, LED3.A, LED4.C, R20.2
unnamed: LED3.C, LED4.A, LED5.C, LED6.A, R22.2
unnamed: R32.2, X2.D-
unnamed: R31.2, X2.D+
unnamed: LED15.C, LED16.A, LED17.A, LED18.C, R53.2
unnamed: LED13.A, LED14.C, LED17.C, LED18.A, R52.2
unnamed: LED13.C, LED14.A, LED15.A, LED16.C, R54.2
unnamed: F2.1, X2.VBUS
unnamed: LED12.C, R39.2
unnamed: LED22.A, R57.1
unnamed: LED21.A, R58.1
unnamed: LED20.A, R55.1
unnamed: LED19.A, R56.1
PD1: LED20.C, LED22.C, U2.22
PD5: LED9.C, LED11.C, U1.22
PULL-UP: R4.2, R5.2, R6.2, R7.2, R8.2, R9.2, R10.2, R11.2, R12.2, R13.2, R14.2, R15.2, SJ1.2
PULL-UP1: R40.2, R41.2, R42.2, R43.2, R44.2, R45.2, R46.2, R47.2, R48.2, R49.2, R50.2, R51.2, SJ2.2
RESET: JP14.2, JP14.2-2, R3.1, U1.13
RESET1: JP26.2, JP26.2-2, R30.1, U2.13
VCC: C5.2, C6.2, C7.A, C8.2, F1.2, JP14.4, JP14.4-2, LED7.A, R3.2, R16.2, R17.2, R18.2, R19.2, R24.2, R25.2, R26.2, R27.2, R28.2, R29.2, SJ1.1, U1.2, U1.7, U1.14, U1.24, U1.34, U1.44
VCC1: C13.2, C14.2, C15.A, C16.2, F2.2, JP26.4, JP26.4-2, LED12.A, R30.2, R33.2, R34.2, R35.2, R36.2, R37.2, R38.2, R55.2, R56.2, R57.2, R58.2, SJ2.1, U2.2, U2.7, U2.14, U2.24, U2.34, U2.44

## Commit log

2012-05-18 initial commit of design files
2012-06-05 v1.2 of MaKey MaKey renamed files to remove version number
2012-06-15 Adding panelized MaKey MaKey eagle files and its gerbers
2012-06-15 Ammending BOM a bit.
2012-08-14 Initial commit of code (1.4.1 - first live version) Initial commit of MaKey MaKey Arduino addon (hardware directory)
2012-08-28 Fixed problem with "click" LED lighting up whenever the "up" LED lights up.
    It appears there should only be one of the inputs set to HIGH for each
    display LED. With two set to HIGH, it caused another led to be lit at
    low power.
2013-03-07 filling out blank readme with basic information
2013-09-03 Cleaning up repo structure
2013-09-03 Fixing README typos
2013-12-05 QC Revision
    1.) Switch 0402 to 0603 footprints
    2.) Updated to wide PTC footprint
    3.) Added more bstop over lead banks on 32u4 IC for better AOI.
2013-12-10 Swapped positions of PTC and C8
    Swapped the positions of PTC and C8 to better accommodate and center the
    "POWER" silk.
2014-01-09 Deleted old v12 panel. Created new v13 Giant Panel
2014-05-05 Updating README with collaboration information
2014-11-14 Fixed typo in makey_makey.ino
2015-08-03 changed folder format
2015-08-12 Changing width of polygons from 0 to 0.001
    Polygons on bPlace, tPlace and top copper layers are affected.
    This makes generating gerber files from the board _much_ faster. Shouldn't
    have any visible effect on the appearance of the board.
2015-08-12 Upping version to 1.4
    Removing old changelog from schematic's second sheet.
2015-08-27 Signed the Windows driver
2015-09-11 added trademark notice to README
2015-09-14 Fixing typos.
2015-11-25 Adding Mouse and Keyboard library includes
2015-11-25 Updating boards adding platforms.txt for 1.6.6 compatibility
2016-01-21 Adding Arduino version check to Mouse and Keyboard h file includes
2018-03-28 Update README.md
    Add retired note.

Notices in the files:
parts and their libraries:
SparkFun-DigitalIC: Licensing: CC v3.0 Share-Alike You are welcome to use this library for commercial purposes.
SparkFun-Aesthetics: Released under the Creative Commons
SparkFun-Aesthetics: http://creativecommons.org/licenses/by-sa/3.0
